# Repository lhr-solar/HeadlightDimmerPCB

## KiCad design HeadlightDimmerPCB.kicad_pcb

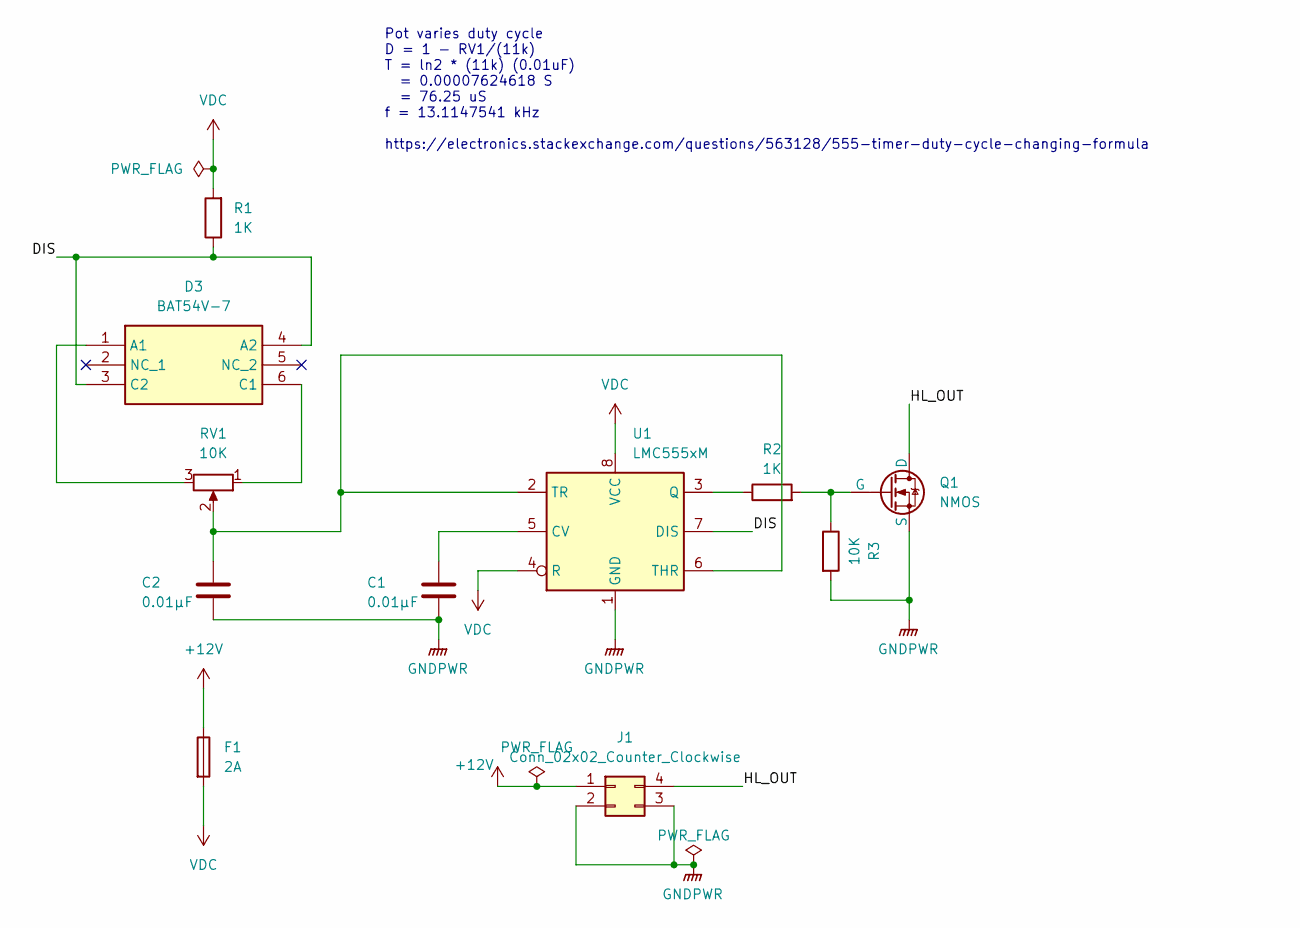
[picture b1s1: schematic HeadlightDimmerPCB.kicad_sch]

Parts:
C1, C2: 0.01µF; C_0805_2012Metric_Pad1.18x1.45mm_HandSolder
D3: BAT54V-7; SOT-563; Mouser Part Number 621-BAT54V-7
F1: 2A; Fuse_1206_3216Metric
J1: Conn_02x02_Counter_Clockwise; CONN04_0757571121_MOL
Q1: NMOS; SOT-23
R1, R2: 1K; R_0805_2012Metric_Pad1.20x1.40mm_HandSolder
R3: 10K; R_0805_2012Metric_Pad1.20x1.40mm_HandSolder
RV1: 10K; Potentiometer_ACP_CA6-VSMD_Vertical_Hole
U1: LMC555xM; SOIC-8_3.9x4.9mm_P1.27mm

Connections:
+12V: F1.1, J1.1
/DIS: D3.3 (C2), D3.4 (A2), R1.1, U1.7 (DIS)
/HL_OUT: J1.4, Q1.1 (D)
GNDPWR: C1.2, C2.2, J1.2, J1.3, Q1.3 (S), R3.2, U1.1 (GND)
unnamed: D3.1 (A1), RV1.3
unnamed: D3.6 (C1), RV1.1
unnamed: Q1.2 (G), R2.2, R3.1
unnamed: C1.1, U1.5 (CV)
unnamed: R2.1, U1.3 (Q)
unnamed: C2.1, RV1.2, U1.2 (TR), U1.6 (THR)
VDC: F1.2, R1.2, U1.4 (R), U1.8 (VCC)

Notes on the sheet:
Pot varies duty cycle D = 1 - RV1/(11k) T = ln2 * (11k) (0.01uF) = 0.00007624618 S = 76.25 uS f = 13.1147541 kHz https://electronics.stackexchange.com/questions/563128/555-timer-duty-cycle-changing-formula

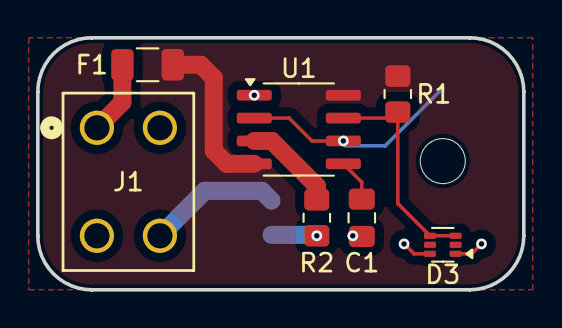
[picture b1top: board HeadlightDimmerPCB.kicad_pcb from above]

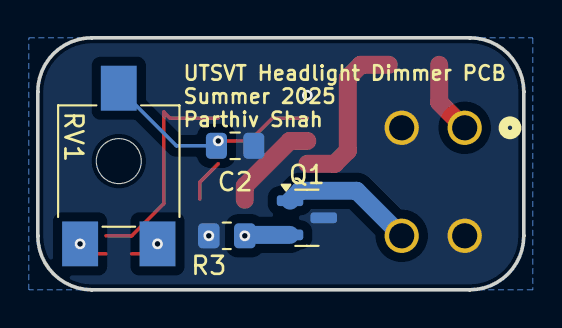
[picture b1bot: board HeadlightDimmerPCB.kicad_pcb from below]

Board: 2 copper layers, 27.0 x 14.0 mm, 11 parts (4 on the bottom side), 11 nets.

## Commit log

2025-05-26 gitignore
2025-05-26 bah2
2025-05-27 more routing and part selection
2025-05-31 final
2025-06-02 production gerbers
